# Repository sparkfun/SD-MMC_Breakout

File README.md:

SD-MMC Breakout Board
=====================

[
*SD-MMC Breakout Board(BOB-12941)*](https://www.sparkfun.com/products/12941)

This breakout board allows you to breakout the SD/MMC socket to a standard 0.1" 10-pin header. 

Repository Contents
-------------------
* **/Fritzing** - Fritzing diagram for the board (.fzpz)
* **/Hardware** - All Eagle design files (.brd, .sch)
* **/Production** - Test bed files and production panel files

Version History
---------------
* [v20](https://www.sparkfun.com/products/retired/11403) Version 2.0 with old SD socket footprint

License Information
-------------------
The hardware is released under [Creative Commons ShareAlike 4.0 International](https://creativecommons.org/licenses/by-sa/4.0/).

Distributed as-is; no warranty is given.

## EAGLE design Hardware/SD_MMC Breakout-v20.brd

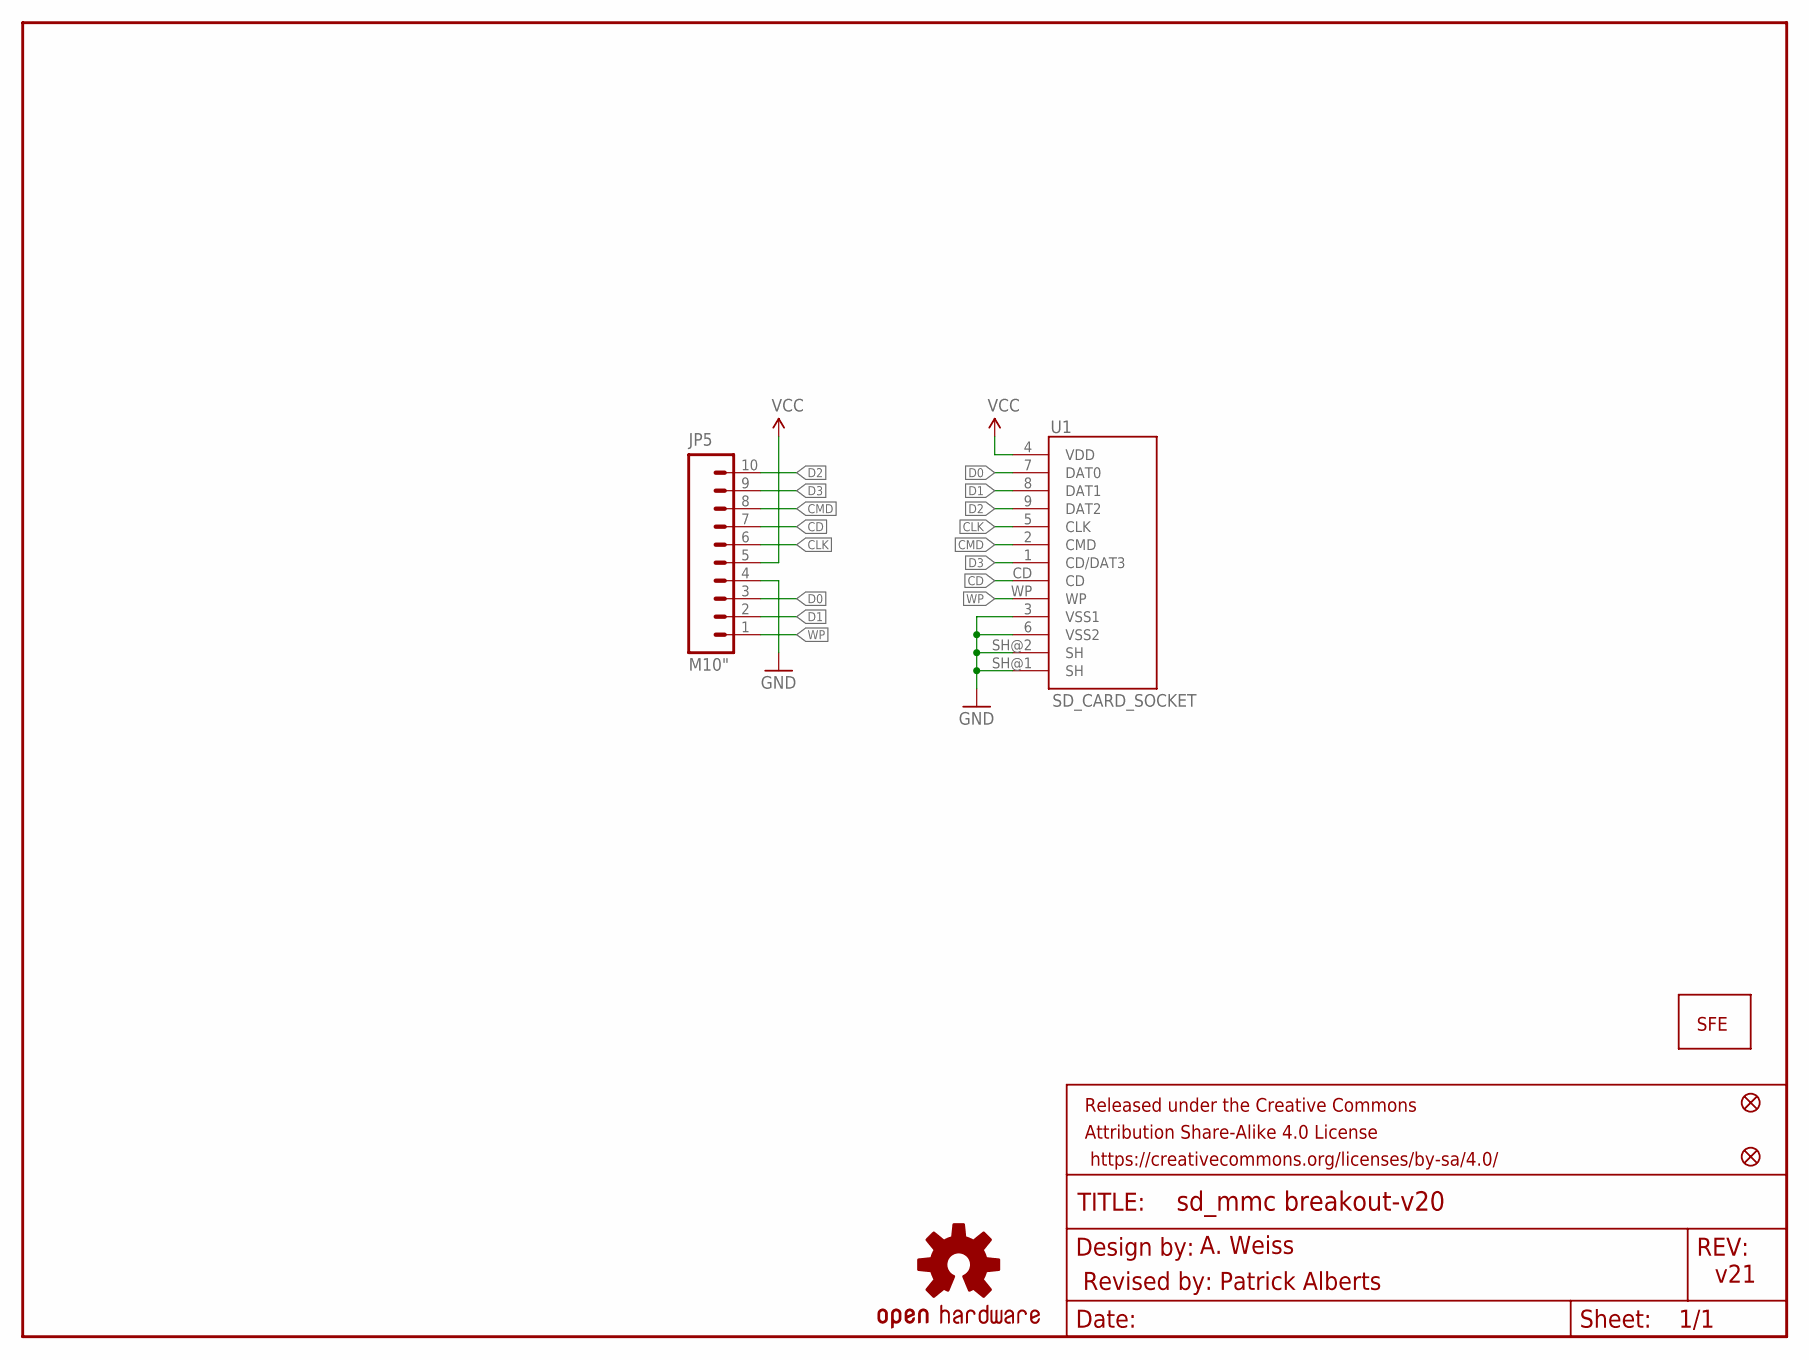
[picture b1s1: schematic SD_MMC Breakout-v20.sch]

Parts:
FID1, FID2: FIDUCIAL1X2; FIDUCIAL-1X2
FRAME1: FRAME-LETTER; CREATIVE_COMMONS
JP5: M10"; 1X10
U1: SD_CARD_SOCKET; SD_1:1
U$1: LOGO-SFENEW; SFE-NEW-WEBLOGO
U$3: OSHW-LOGOS; OSHW-LOGO-S

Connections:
CD: JP5.7, U1.CD
CLK: JP5.6, U1.5 (CLK)
CMD: JP5.8, U1.2 (CMD)
D0: JP5.3, U1.7 (DAT0)
D1: JP5.2, U1.8 (DAT1)
D2: JP5.10, U1.9 (DAT2)
D3: JP5.9, U1.1 (CD/DAT3)
GND: JP5.4, U1.3 (VSS1), U1.6 (VSS2), U1.SH@1 (SH), U1.SH@2 (SH)
VCC: JP5.5, U1.4 (VDD)
WP: JP5.1, U1.WP

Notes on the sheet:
A. Weiss
Revised by: Patrick Alberts
v21

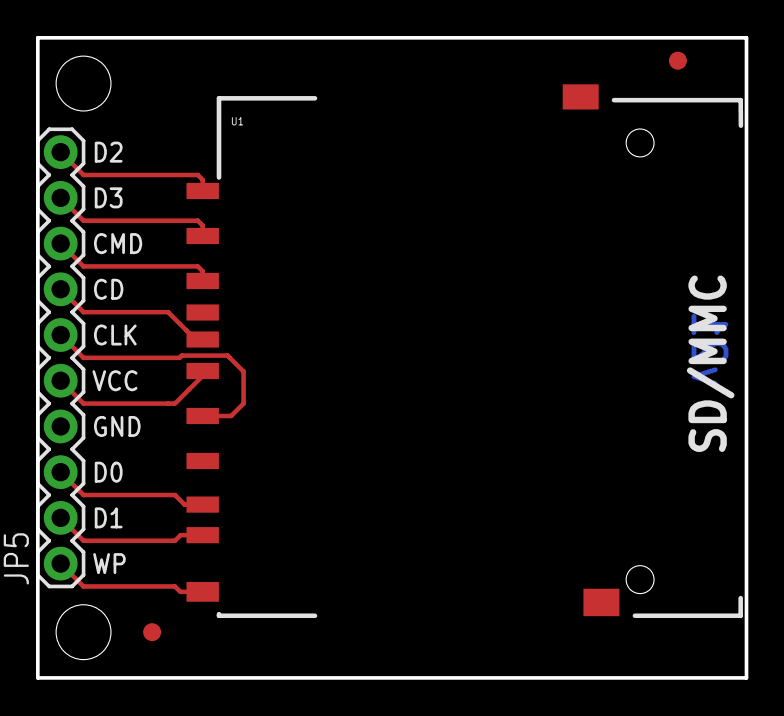
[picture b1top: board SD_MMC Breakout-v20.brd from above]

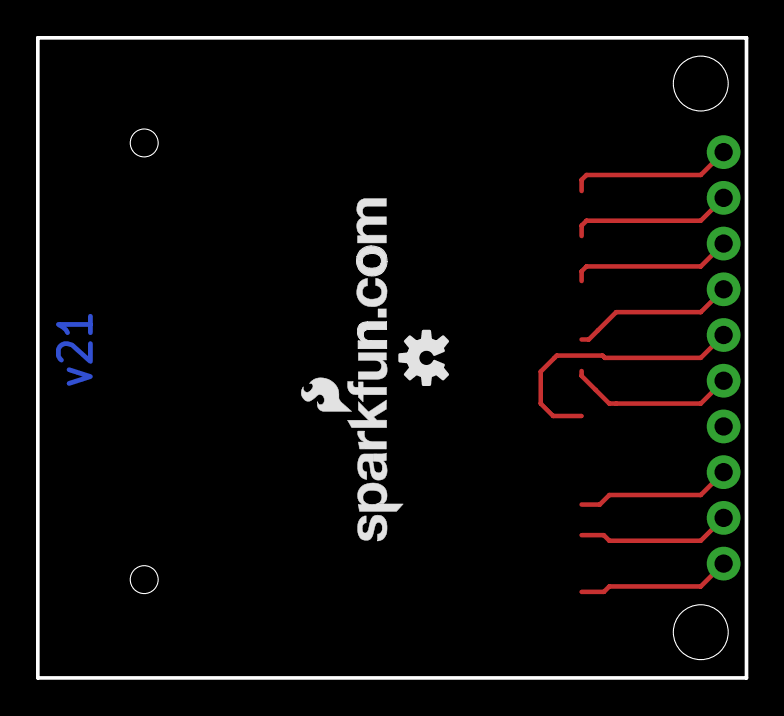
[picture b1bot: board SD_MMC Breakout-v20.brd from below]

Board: 2 copper layers, 39.4 x 35.6 mm, 9 parts (2 on the bottom side), 10 nets.

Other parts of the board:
U$4, U$5: STAND-OFF-TIGHT

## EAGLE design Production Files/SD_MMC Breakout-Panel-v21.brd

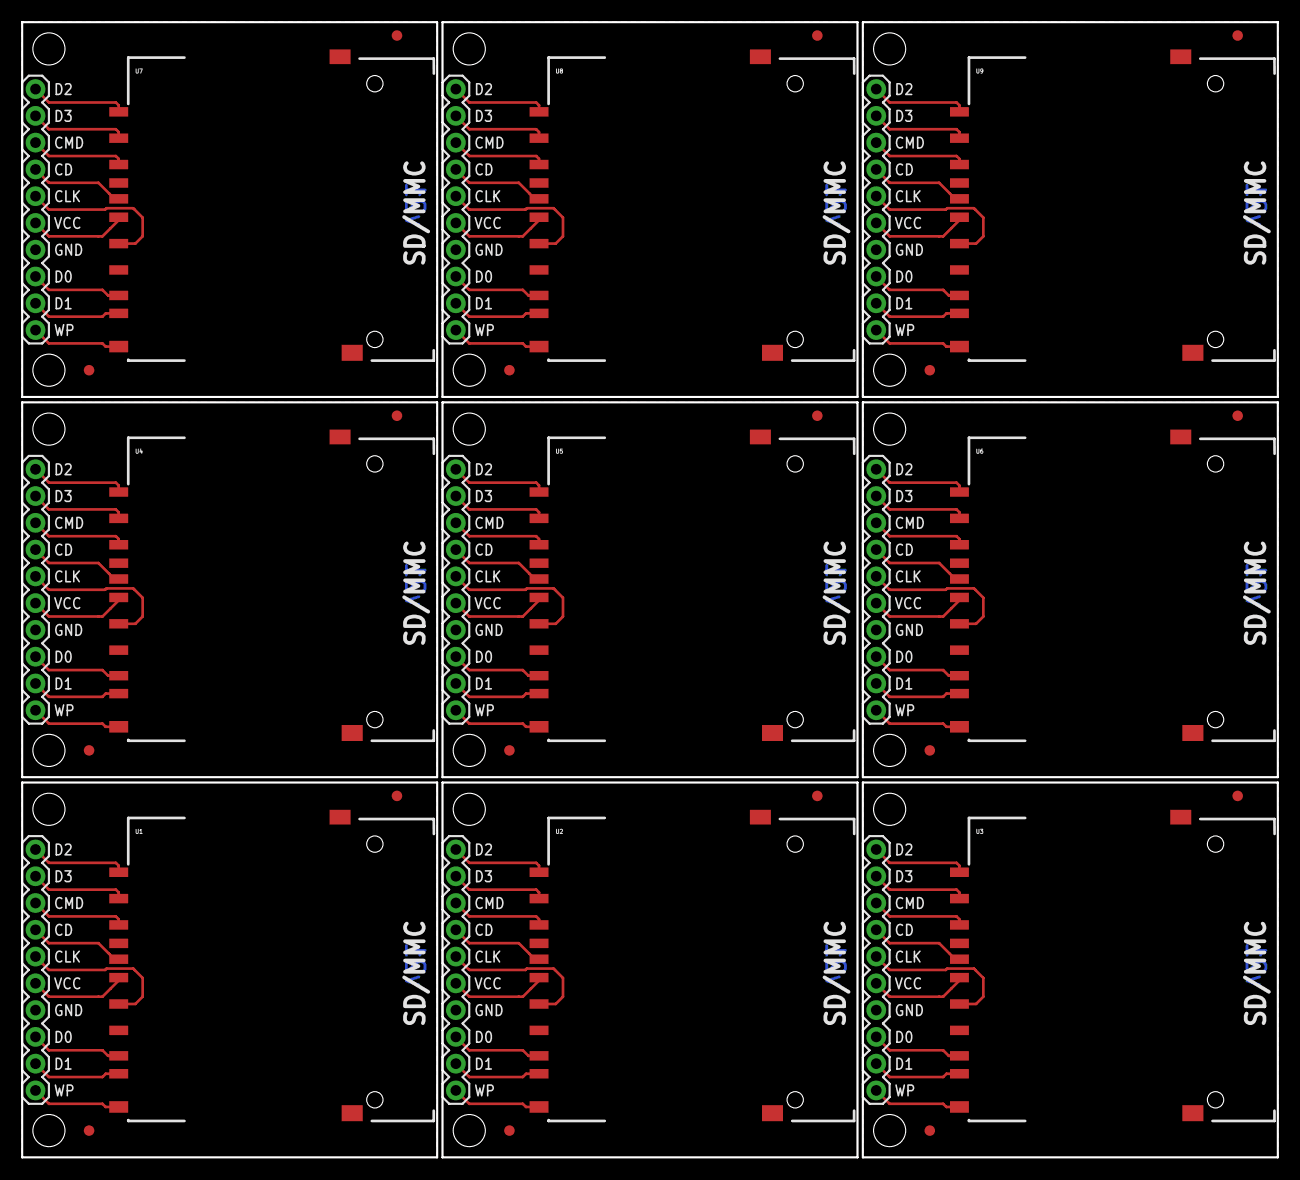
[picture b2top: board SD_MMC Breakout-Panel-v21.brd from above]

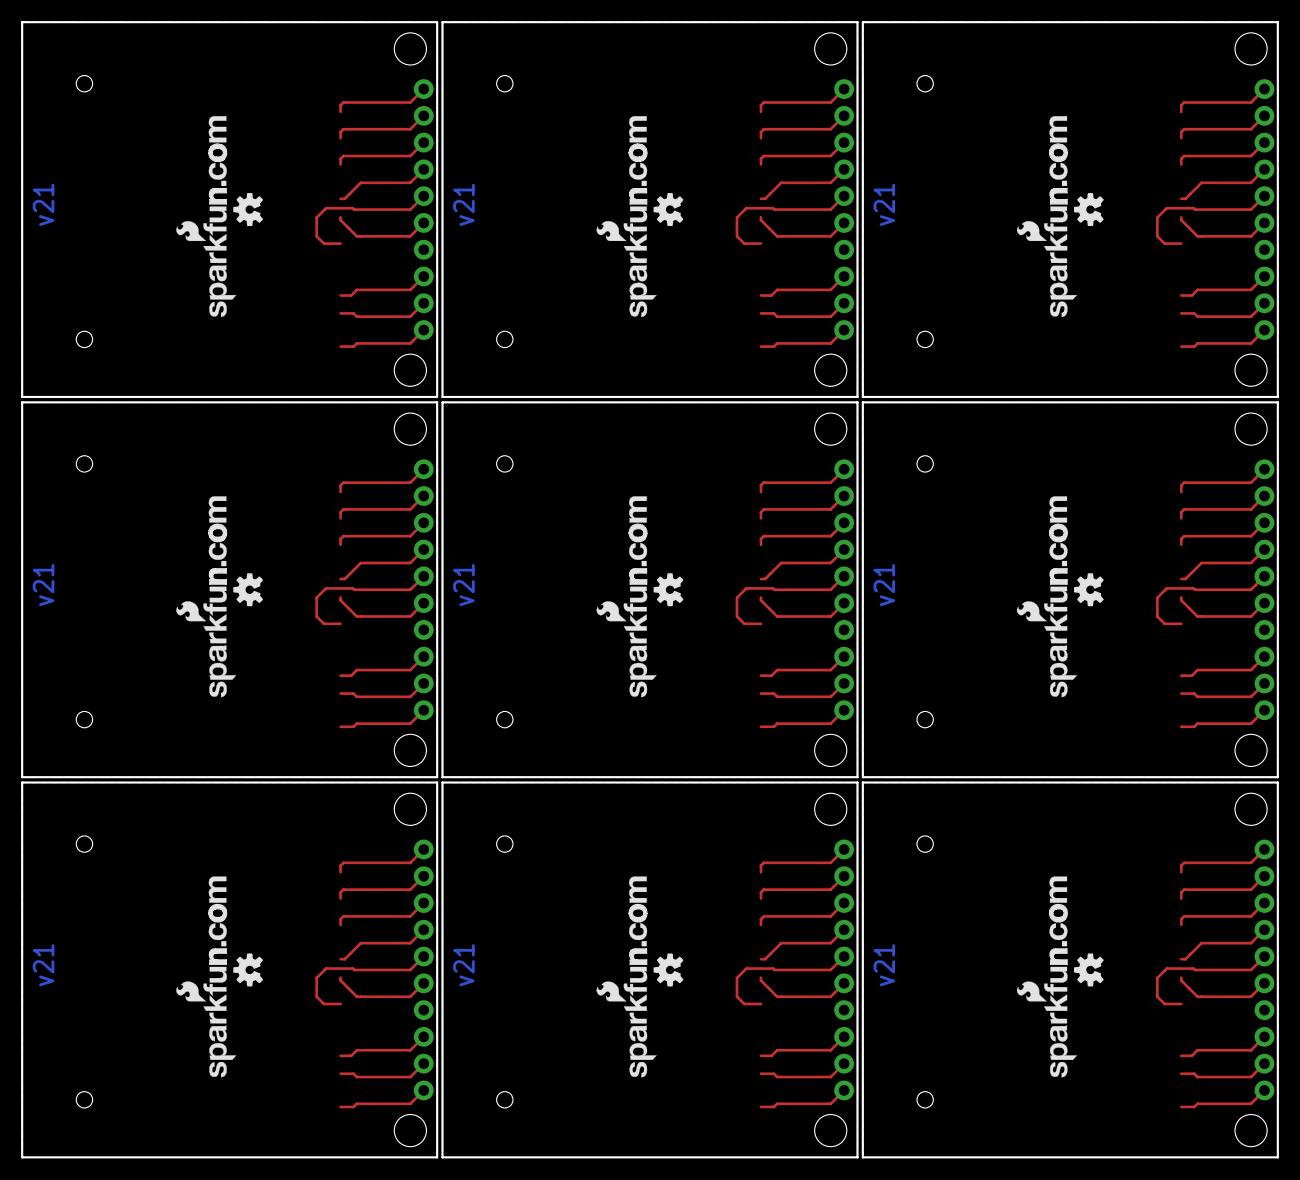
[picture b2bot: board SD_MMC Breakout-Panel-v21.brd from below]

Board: 2 copper layers, 119.1 x 107.7 mm, 72 parts (18 on the bottom side), 90 nets.

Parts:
FID1, FID2, FID3, FID4, FID5, FID6, FID7, FID8, FID9, FID10, FID11, FID12, FID13, FID14, FID15, FID16, FID17, FID18: FIDUCIAL1X2; FIDUCIAL-1X2
JP1, JP2, JP3, JP4, JP5, JP6, JP7, JP8, JP9: M10"; 1X10
U1, U2, U3, U4, U5, U6, U7, U8, U9: SD_CARD_SOCKET; SD_1:1
U$1, U$2, U$9, U$13, U$17, U$21, U$25, U$29, U$33: LOGO-SFENEW; SFE-NEW-WEBLOGO
U$3, U$6, U$10, U$14, U$18, U$22, U$26, U$30, U$34: OSHW-LOGOS; OSHW-LOGO-S
U$4, U$5, U$7, U$8, U$11, U$12, U$15, U$16, U$19, U$20, U$23, U$24, U$27, U$28, U$31, U$32, U$35, U$36: STAND-OFF-TIGHT

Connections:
CD: JP5.7, U1.CD
CD1: JP1.7, U2.CD
CD2: JP2.7, U3.CD
CD3: JP3.7, U4.CD
CD4: JP4.7, U5.CD
CD5: JP6.7, U6.CD
CD6: JP7.7, U7.CD
CD7: JP8.7, U8.CD
CD8: JP9.7, U9.CD
CLK: JP5.6, U1.5
CLK1: JP1.6, U2.5
CLK2: JP2.6, U3.5
CLK3: JP3.6, U4.5
CLK4: JP4.6, U5.5
CLK5: JP6.6, U6.5
CLK6: JP7.6, U7.5
CLK7: JP8.6, U8.5
CLK8: JP9.6, U9.5
CMD: JP5.8, U1.2
CMD1: JP1.8, U2.2
CMD2: JP2.8, U3.2
CMD3: JP3.8, U4.2
CMD4: JP4.8, U5.2
CMD5: JP6.8, U6.2
CMD6: JP7.8, U7.2
CMD7: JP8.8, U8.2
CMD8: JP9.8, U9.2
D0: JP5.3, U1.7
D1: JP5.2, U1.8
D2: JP5.10, U1.9
D3: JP5.9, U1.1
D4: JP1.2, U2.8
D5: JP1.3, U2.7
D6: JP1.10, U2.9
D7: JP1.9, U2.1
D8: JP2.2, U3.8
D9: JP2.3, U3.7
D10: JP2.10, U3.9
D11: JP2.9, U3.1
D12: JP3.2, U4.8
D13: JP3.3, U4.7
D14: JP3.10, U4.9
D15: JP3.9, U4.1
D16: JP4.2, U5.8
D17: JP4.3, U5.7
D18: JP4.10, U5.9
D19: JP4.9, U5.1
D20: JP6.2, U6.8
D21: JP6.3, U6.7
D22: JP6.10, U6.9
D23: JP6.9, U6.1
D24: JP7.2, U7.8
D25: JP7.3, U7.7
D26: JP7.10, U7.9
D27: JP7.9, U7.1
D28: JP8.2, U8.8
D29: JP8.3, U8.7
D30: JP8.10, U8.9
D31: JP8.9, U8.1
D32: JP9.2, U9.8
D33: JP9.3, U9.7
D34: JP9.10, U9.9
D35: JP9.9, U9.1
GND: JP5.4, U1.3, U1.6, U1.SH@1, U1.SH@2
GND1: JP1.4, U2.3, U2.6, U2.SH@1, U2.SH@2
GND2: JP2.4, U3.3, U3.6, U3.SH@1, U3.SH@2
GND3: JP3.4, U4.3, U4.6, U4.SH@1, U4.SH@2
GND4: JP4.4, U5.3, U5.6, U5.SH@1, U5.SH@2
GND5: JP6.4, U6.3, U6.6, U6.SH@1, U6.SH@2
GND6: JP7.4, U7.3, U7.6, U7.SH@1, U7.SH@2
GND7: JP8.4, U8.3, U8.6, U8.SH@1, U8.SH@2
GND8: JP9.4, U9.3, U9.6, U9.SH@1, U9.SH@2
VCC: JP5.5, U1.4
VCC1: JP1.5, U2.4
VCC2: JP2.5, U3.4
VCC3: JP3.5, U4.4
VCC4: JP4.5, U5.4
VCC5: JP6.5, U6.4
VCC6: JP7.5, U7.4
VCC7: JP8.5, U8.4
VCC8: JP9.5, U9.4
WP: JP5.1, U1.WP
WP1: JP1.1, U2.WP
WP2: JP2.1, U3.WP
WP3: JP3.1, U4.WP
WP4: JP4.1, U5.WP
WP5: JP6.1, U6.WP
WP6: JP7.1, U7.WP
WP7: JP8.1, U8.WP
WP8: JP9.1, U9.WP

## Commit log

2014-02-06 Board file commit
2014-04-26 Added standoffs, sch work
2014-05-02 Updated Sch
2014-05-02 added new sd socket
2014-05-06 Changed Font, Removed Extra Pins
2014-05-07 Add the Fritzing part.
2014-05-08 Update Fritzing part : - renamed the file to match with others ; - Make real holes in the PCB svg, instead of fake white circles ; - Set all pins type as 'male' instead of 'pad', to match with other 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
2014-05-13 Fixing repo structure and updating README
2014-05-20 changed fiducial to regular size
2014-05-20 Created panel v21
2014-08-08 Updating README to new links

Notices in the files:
parts and their libraries:
SparkFun-Connectors: Licensing: CC v3.0 Share-Alike You are welcome to use this library for commercial purposes.
SparkFun-Aesthetics: Released under the Creative Commons Attribution Share-Alike 4.0 License
SparkFun-Aesthetics: Released under the Creative Commons
